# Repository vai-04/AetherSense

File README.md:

# 🌐 AetherSense – Intelligent Environmental Monitoring System

## 📌 Project Overview
AetherSense is an IoT-based environmental monitoring system designed to improve energy efficiency and indoor comfort.

Traditional HVAC systems are **occupancy-blind**, leading to energy wastage.  
This project solves that using:
- Multi-sensor data fusion  
- Real-time monitoring  
- Machine learning  

---

## 🧠 Key Features
- 🌡️ Temperature & humidity monitoring  
- 🔊 Sound-based occupancy detection  
- 💡 Light intensity tracking  
- 📊 Real-time dashboard visualization  
- 🚨 Alert system (Normal / Warning / Critical)  
- 🤖 Machine learning classification (Safe / Unsafe)  
- ☁️ Cloud-based data storage  

---

## 🏗️ System Architecture

## Schematics

## PCB

### 🔹 Architecture Layers

| Layer | Description |
|------|------------|
| Sensing Layer | Collects environmental data using sensors |
| Processing Layer | RP2040 processes data |
| Cloud Layer | Stores data & runs ML model |
| Application Layer | Dashboard visualization |

---

## 🔧 Hardware Components

- RP2040 Microcontroller  
- DHT11 Temperature & Humidity Sensor  
- LM393 Sound Sensor  
- LDR Light Sensor  
- Breadboard & Connections  

---

## 💻 Software Architecture

### 🔄 Processing Pipeline

---

## 📊 Feature Vector

---

## 🤖 Machine Learning Model

| Parameter | Value |
|----------|------|
| Model | Random Forest |
| Input | Sensor Feature Vector |
| Output | Room Condition |
| Accuracy | 99.85% |

---

## 📈 Experimental Results

| Metric | Value |
|-------|------|
| Training Samples | 8103 |
| Test Samples | 2026 |
| Accuracy | 99.85% |
| OOB Accuracy | 99.75% |

---

## 🔄 System Workflow

1. Initialize system  
2. Read sensor data  
3. Process & classify values  
4. Create feature vector  
5. Perform ML inference  
6. Update dashboard  
7. Generate alerts  
8. Store data  

---

## 🚨 Alert Levels

| Level | Meaning |
|------|--------|
| 🟢 Normal | All values safe |
| 🟡 Warning | Moderate deviation |
| 🔴 Critical | Unsafe condition |

---

## 📊 Dashboard Features
- Live sensor values  
- Graphs & trends  
- System status  
- Prediction with confidence  
- Alert panel  

---

## ⚠️ Limitations
- Slow DHT11 response (5s delay)  
- Sound sensor noise sensitivity  
- Light sensor affected by weather  
- Dataset imbalance  
- Requires continuous connectivity  

---

## 🚀 Future Scope
- Faster sensors  
- Large-scale deployment  
- Better occupancy detection  
- Wireless communication  
- Adaptive ML models  

---

## 🎯 Conclusion
AetherSense provides a **smart, scalable, and cost-effective solution** for intelligent environmental monitoring using IoT and Machine Learning.

---

## 📚 References
- RP2040 Datasheet  
- DHT11 Sensor Manual  
- LM393 Datasheet  
- Kaggle Dataset  
- Random Forest Algorithm  

---

## 📄 License
This project is for academic purposes.

## 👥 Team Members
| Name | Roll Number |
|------|------------|
| Aditi Akansha | 25BCE0544 |
| Vaibhav Singh | 25BCE2492 |
| Gowshik R S | 25BCE0958 |
| Shashank Pulipati | 25BEC0573 |
| H Sharman Singh | 25BEC0076 |

---

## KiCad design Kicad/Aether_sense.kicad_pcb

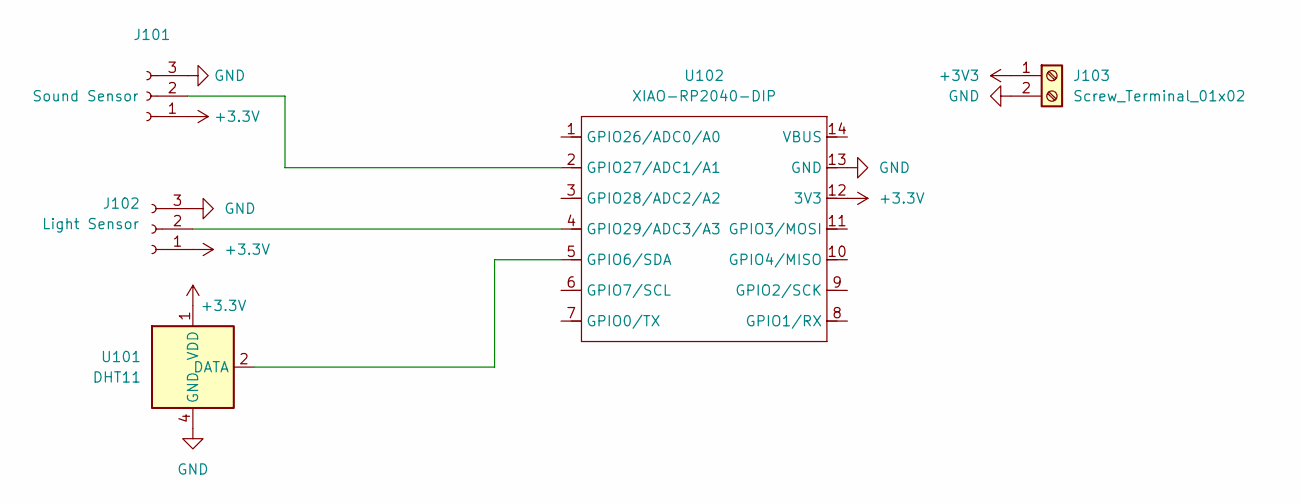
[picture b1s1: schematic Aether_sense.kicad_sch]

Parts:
J101: Sound Sensor; PinSocket_1x03_P2.54mm_Vertical
J102: Light Sensor; PinSocket_1x03_P2.54mm_Vertical
J103: Screw_Terminal_01x02; TerminalBlock_Xinya_XY308-2.54-2P_1x02_P2.54mm_Horizontal
U101: DHT11; Aosong_DHT11_5.5x12.0_P2.54mm
U102: XIAO-RP2040-DIP; MCU_Seeed_ESP32C3

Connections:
+3.3V: J101.1, J102.1, U101.1 (VDD), U102.12 (3V3)
+3V3: J103.1
GND: J101.3, J102.3, J103.2, U101.4 (GND), U102.13 (GND)
unnamed: J101.2, U102.2 (GPIO27/ADC1/A1)
unnamed: J102.2, U102.4 (GPIO29/ADC3/A3)
unnamed: U101.2 (DATA), U102.5 (GPIO6/SDA)

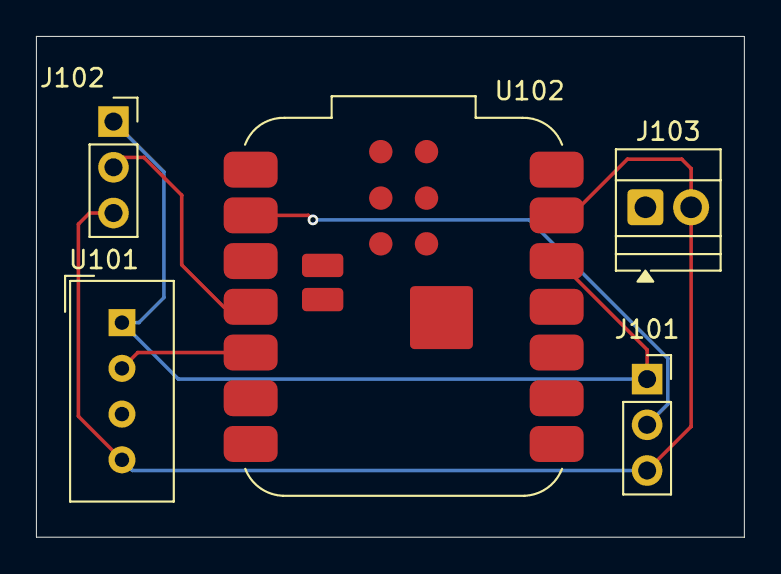
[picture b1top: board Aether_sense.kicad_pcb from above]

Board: 2 copper layers, 39.3 x 27.8 mm, 5 parts (0 on the bottom side), 5 nets.

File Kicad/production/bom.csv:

Designator,Footprint,Quantity,Value,LCSC Part #
J101,PinSocket_1x03_P2.54mm_Vertical,1,Sound Sensor,
J102,PinSocket_1x03_P2.54mm_Vertical,1,Light Sensor,
J103,TerminalBlock_Xinya_XY308-2.54-2P_1x02_P2.54mm_Horizontal,1,power,
U101,Aosong_DHT11_5.5x12.0_P2.54mm,1,DHT11,
U102,MCU_Seeed_ESP32C3,1,XIAO-RP2040-DIP,
